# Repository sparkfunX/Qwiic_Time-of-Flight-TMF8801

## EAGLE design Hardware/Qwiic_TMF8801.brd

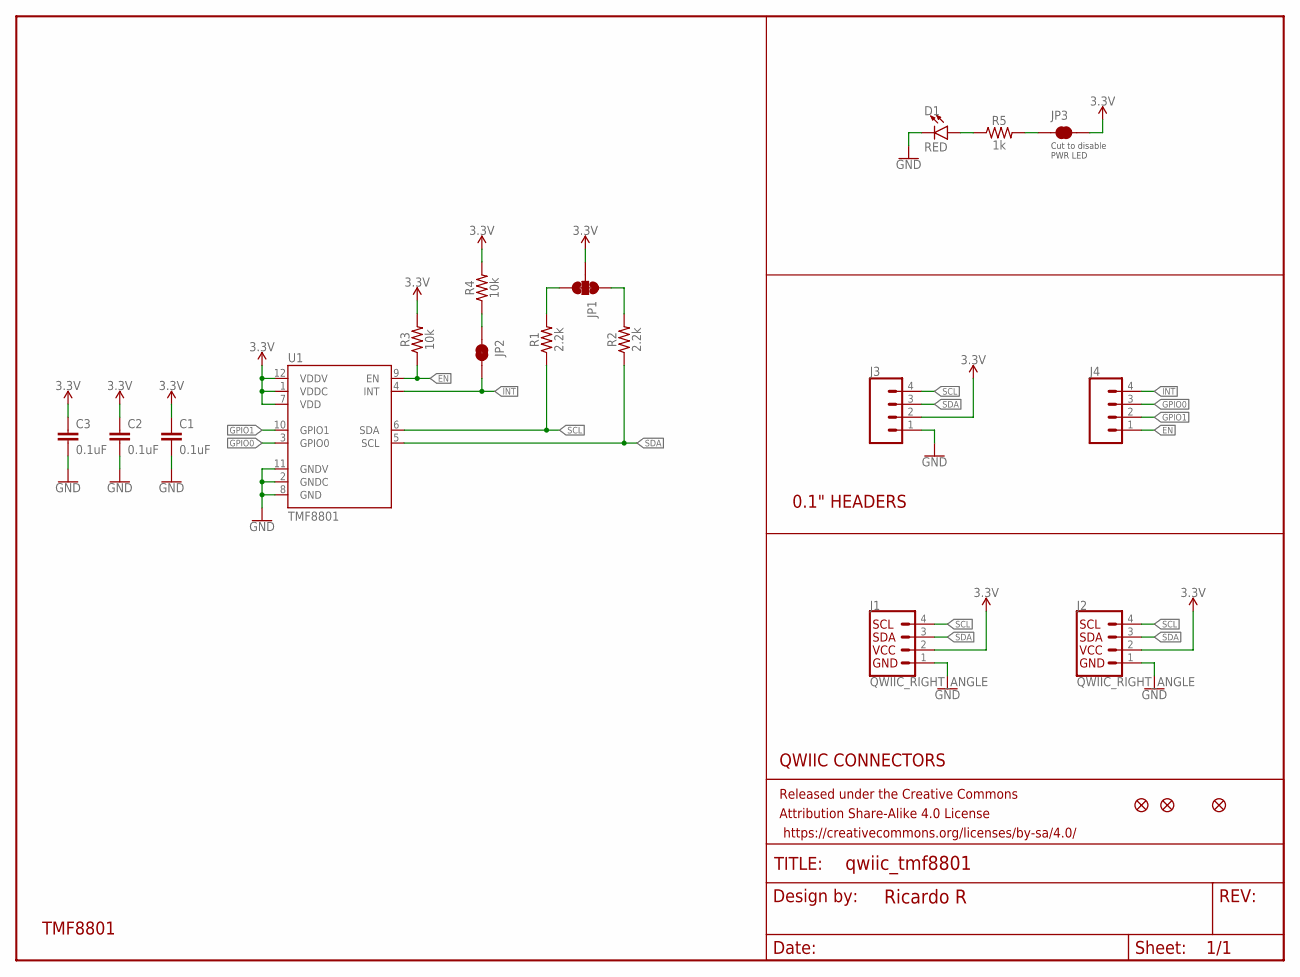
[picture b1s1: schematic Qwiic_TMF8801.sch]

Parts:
C1, C2, C3: 0.1uF; 0603
D1: RED; LED-0603
FD1, FD3, FD4: FIDUCIAL1X2; FIDUCIAL-1X2
FRAME1: FRAME-LETTERNO_PACKAGE; DUMMY
J1, J2: QWIIC_RIGHT_ANGLE; JST04_1MM_RA
J3, J4: CONN_041X04_NO_SILK; 1X04_NO_SILK
JP1: JUMPER-SMT_3_2-NC_TRACE_SILK; SMT-JUMPER_3_2-NC_TRACE_SILK
JP2, JP3: JUMPER-SMT_2_NC_TRACE_SILK; SMT-JUMPER_2_NC_TRACE_SILK
R1, R2: 2.2k; 0603
R3, R4: 10k; 0603
R5: 1k; 0603
U1: TMF8801; TMF8801-CUSTOM

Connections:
3.3V: C1.1, C2.1, C3.1, J1.2, J2.2, J3.2, JP1.2, JP3.2, R3.2, R4.2, U1.1 (VDDC), U1.7 (VDD), U1.12 (VDDV)
!INT: J4.4, JP2.2, U1.4 (INT)
EN: J4.1, R3.1, U1.9 (EN)
GND: C1.2, C2.2, C3.2, D1.C, J1.1, J2.1, J3.1, U1.2 (GNDC), U1.8 (GND), U1.11 (GNDV)
GPIO0: J4.3, U1.3 (GPIO0)
GPIO1: J4.2, U1.10 (GPIO1)
unnamed: D1.A, R5.1
unnamed: JP1.3, R1.2
unnamed: JP1.1, R2.2
unnamed: JP3.1, R5.2
unnamed: JP2.1, R4.1
SCL: J1.4, J2.4, J3.4, R1.1, U1.6 (SDA)
SDA: J1.3, J2.3, J3.3, R2.1, U1.5 (SCL)

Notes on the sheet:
QWIIC CONNECTORS
0.1" HEADERS
Cut to disable PWR LED
TMF8801

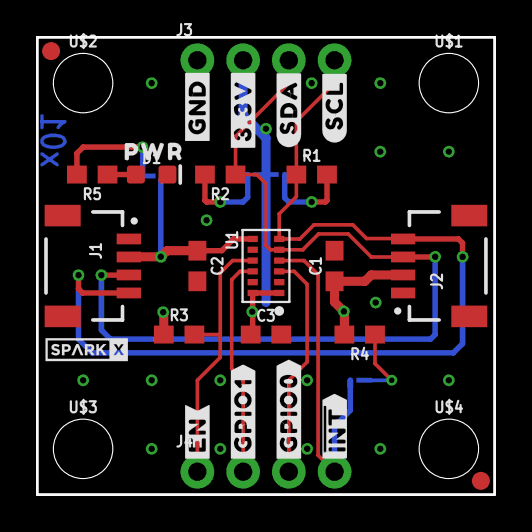
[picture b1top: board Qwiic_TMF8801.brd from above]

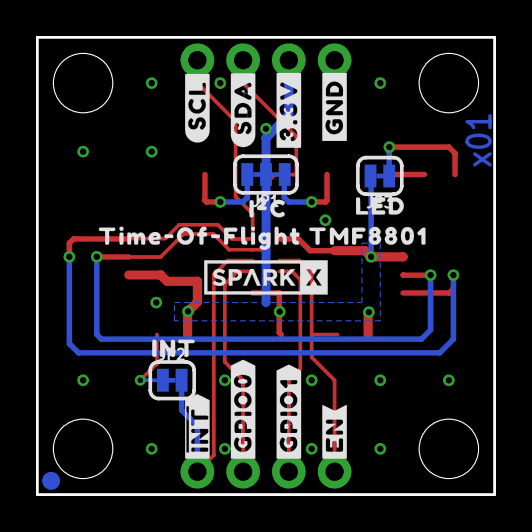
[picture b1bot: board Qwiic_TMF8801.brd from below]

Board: 2 copper layers, 25.4 x 25.4 mm, 48 parts (17 on the bottom side), 13 nets.

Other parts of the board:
U$1, U$2, U$3, U$4: STAND-OFF
U$5, U$17: #3#3V#1
U$6, U$19: #SDA#4
U$7, U$18: #GND#0
U$8, U$24: ##INT##7
U$9, U$25: #GPIO0#7
U$10, U$26: #GPIO1#7
U$11, U$23: #EN#6
U$12: #INT0
U$16: TIME#OF#FLIGHT_TMF88018
U$20: SPARKX-TINY
U$21, U$22: #SCL#5
U$27: SPARKX-SMALL
U$28: I�C0
U$29: LED1
U$30: PWR2

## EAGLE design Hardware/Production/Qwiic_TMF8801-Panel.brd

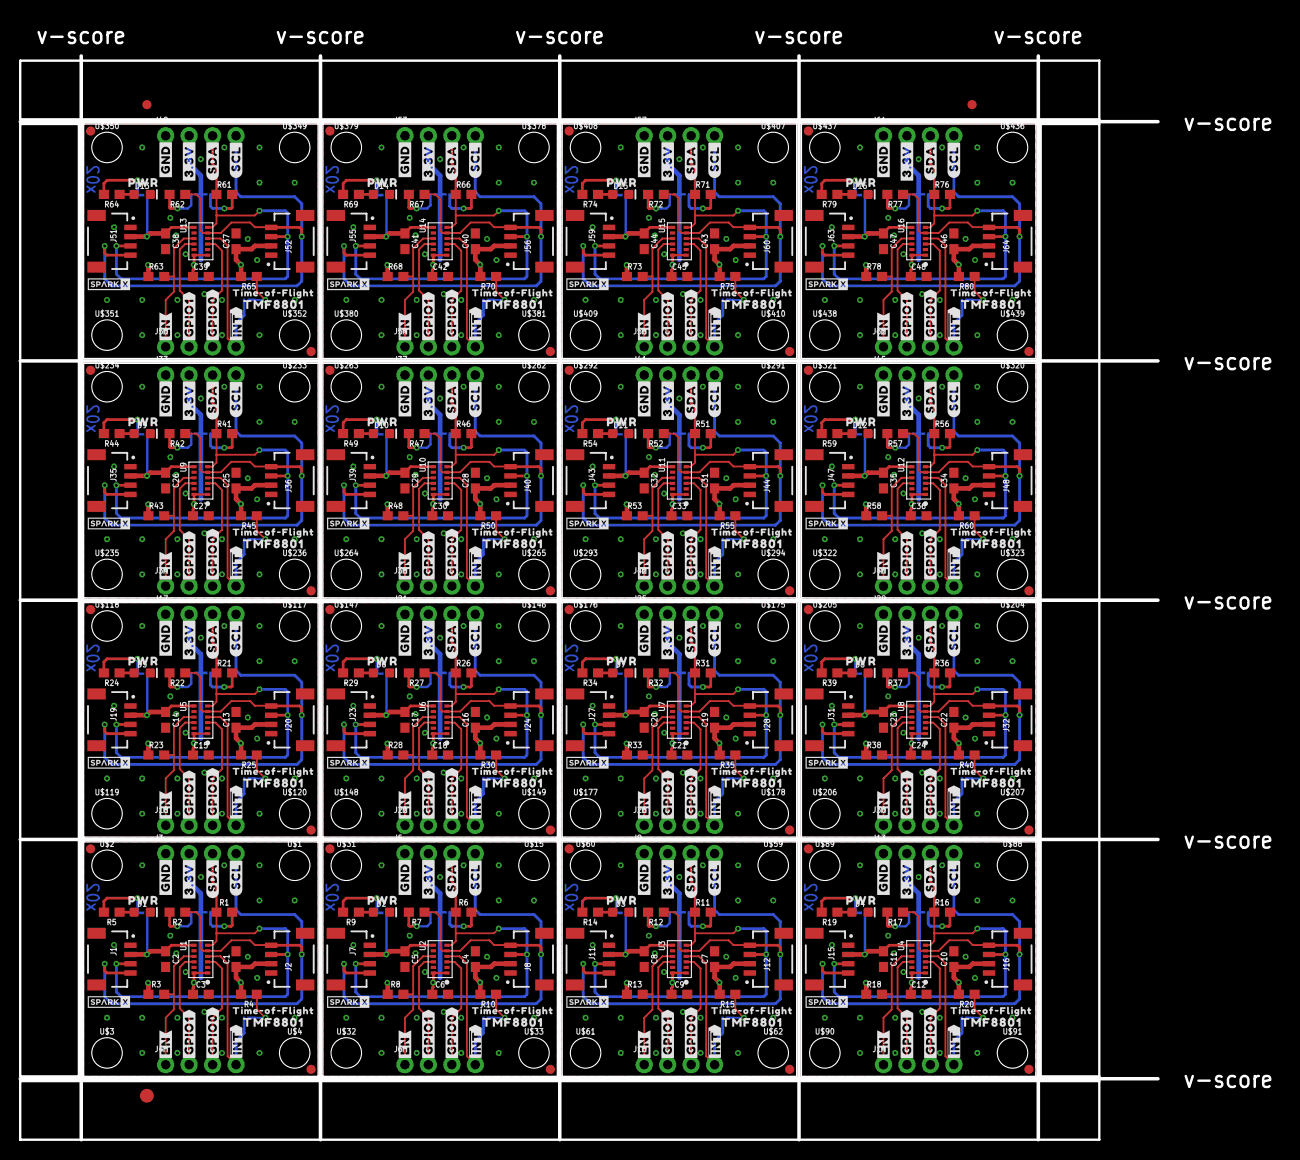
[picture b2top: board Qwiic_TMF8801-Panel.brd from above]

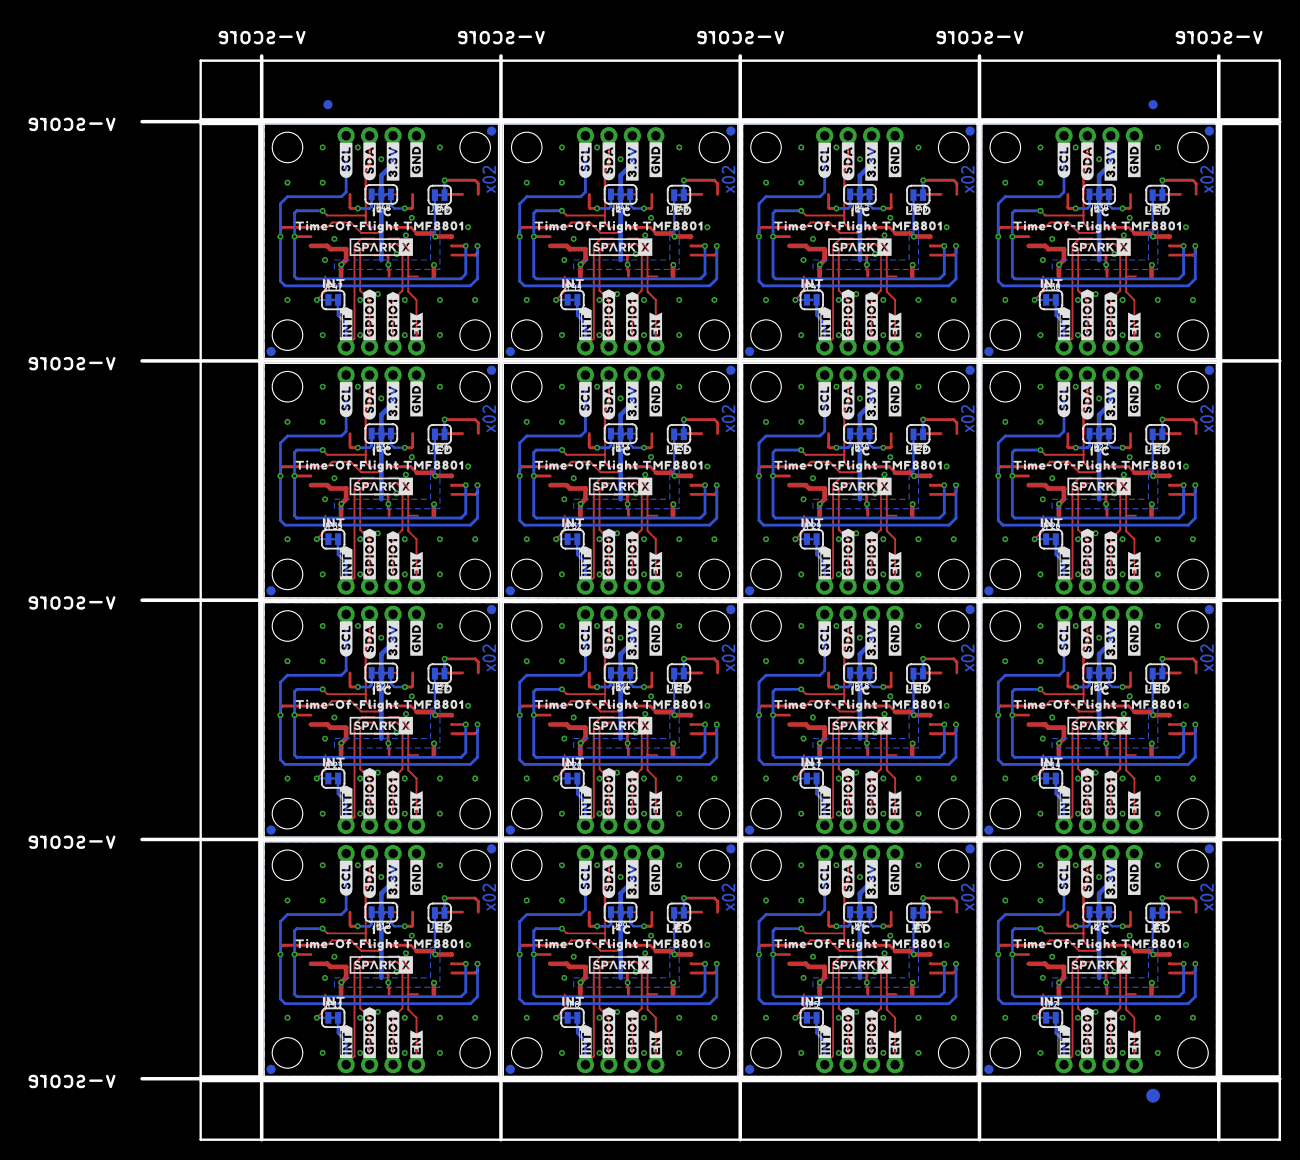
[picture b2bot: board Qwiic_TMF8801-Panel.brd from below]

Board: 2 copper layers, 123.2 x 117.3 mm, 822 parts (291 on the bottom side), 208 nets.

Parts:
C1, C2, C3, C4, C5, C6, C7, C8, C9, C10, C11, C12, C13, C14, C15, C16, C17, C18, C19, C20, C21, C22, C23, C24, C25, C26, C27, C28, C29, C30, C31, C32, C33, C34, C35, C36, C37, C38, C39, C40, C41, C42, C43, C44, C45, C46, C47, C48: 0.1uF; 0603
D1, D2, D3, D4, D5, D6, D7, D8, D9, D10, D11, D12, D13, D14, D15, D16: RED; LED-0603
E$1, E$2, E$3, E$4: FIDUCIAL-1X2
E$5, E$6: FIDUCIAL-1.5X3
FD1, FD2, FD3, FD4, FD5, FD6, FD7, FD8, FD9, FD10, FD11, FD12, FD13, FD14, FD15, FD16, FD17, FD18, FD19, FD20, FD21, FD22, FD23, FD24, FD25, FD26, FD27, FD28, FD29, FD30, FD31, FD32, FD33, FD34, FD35, FD36, FD37, FD38, FD39, FD40, FD41, FD42, FD43, FD44, FD45, FD46, FD47, FD48, FD49, FD50, FD51, FD52, FD53, FD54, FD55, FD56, FD57, FD58, FD59, FD60, FD61, FD62, FD63, FD64: FIDUCIAL1X2; FIDUCIAL-1X2
FRAME1, FRAME2, FRAME3, FRAME4, FRAME5, FRAME6, FRAME7, FRAME8, FRAME9, FRAME10, FRAME11, FRAME12, FRAME13, FRAME14, FRAME15, FRAME16: FRAME-LETTERNO_PACKAGE; DUMMY
J1, J2, J7, J8, J11, J12, J15, J16, J19, J20, J23, J24, J27, J28, J31, J32, J35, J36, J39, J40, J43, J44, J47, J48, J51, J52, J55, J56, J59, J60, J63, J64: Qwiic; JST04_1MM_RA
J3, J4, J5, J6, J9, J10, J13, J14, J17, J18, J21, J22, J25, J26, J29, J30, J33, J34, J37, J38, J41, J42, J45, J46, J49, J50, J53, J54, J57, J58, J61, J62: 1X04_NO_SILK
JP1, JP6, JP9, JP12, JP15, JP18, JP21, JP24, JP27, JP30, JP33, JP36, JP39, JP42, JP45, JP48: JUMPER-SMT_3_2-NC_TRACE_SILK; SMT-JUMPER_3_2-NC_TRACE_SILK
JP2, JP3, JP4, JP5, JP7, JP8, JP10, JP11, JP13, JP14, JP16, JP17, JP19, JP20, JP22, JP23, JP25, JP26, JP28, JP29, JP31, JP32, JP34, JP35, JP37, JP38, JP40, JP41, JP43, JP44, JP46, JP47: JUMPER-SMT_2_NC_TRACE_SILK; SMT-JUMPER_2_NC_TRACE_SILK
R1, R2, R6, R7, R11, R12, R16, R17, R21, R22, R26, R27, R31, R32, R36, R37, R41, R42, R46, R47, R51, R52, R56, R57, R61, R62, R66, R67, R71, R72, R76, R77: 2.2k; 0603
R3, R4, R8, R10, R13, R15, R18, R20, R23, R25, R28, R30, R33, R35, R38, R40, R43, R45, R48, R50, R53, R55, R58, R60, R63, R65, R68, R70, R73, R75, R78, R80: 10k; 0603
R5, R9, R14, R19, R24, R29, R34, R39, R44, R49, R54, R59, R64, R69, R74, R79: 1k; 0603
U1, U2, U3, U4, U5, U6, U7, U8, U9, U10, U11, U12, U13, U14, U15, U16: TMF8801; TMF8801-CUSTOM
U$1, U$2, U$3, U$4, U$15, U$31, U$32, U$33, U$59, U$60, U$61, U$62, U$88, U$89, U$90, U$91, U$117, U$118, U$119, U$120, U$146, U$147, U$148, U$149, U$175, U$176, U$177, U$178, U$204, U$205, U$206, U$207, U$233, U$234, U$235, U$236, U$262, U$263, U$264, U$265, U$291, U$292, U$293, U$294, U$320, U$321, U$322, U$323, U$349, U$350, U$351, U$352, U$378, U$379, U$380, U$381, U$407, U$408, U$409, U$410, U$436, U$437, U$438, U$439: STAND-OFF
U$5, U$17, U$36, U$44, U$65, U$73, U$94, U$102, U$123, U$131, U$152, U$160, U$181, U$189, U$210, U$218, U$239, U$247, U$268, U$276, U$297, U$305, U$326, U$334, U$355, U$363, U$384, U$392, U$413, U$421, U$442, U$450: #3#3V#1
U$6, U$19, U$38, U$46, U$67, U$75, U$96, U$104, U$125, U$133, U$154, U$162, U$183, U$191, U$212, U$220, U$241, U$249, U$270, U$278, U$299, U$307, U$328, U$336, U$357, U$365, U$386, U$394, U$415, U$423, U$444, U$452: #SDA#4
U$7, U$18, U$37, U$45, U$66, U$74, U$95, U$103, U$124, U$132, U$153, U$161, U$182, U$190, U$211, U$219, U$240, U$248, U$269, U$277, U$298, U$306, U$327, U$335, U$356, U$364, U$385, U$393, U$414, U$422, U$443, U$451: #GND#0
U$8, U$24, U$39, U$50, U$68, U$79, U$97, U$108, U$126, U$137, U$155, U$166, U$184, U$195, U$213, U$224, U$242, U$253, U$271, U$282, U$300, U$311, U$329, U$340, U$358, U$369, U$387, U$398, U$416, U$427, U$445, U$456: ##INT##7
U$9, U$25, U$40, U$51, U$69, U$80, U$98, U$109, U$127, U$138, U$156, U$167, U$185, U$196, U$214, U$225, U$243, U$254, U$272, U$283, U$301, U$312, U$330, U$341, U$359, U$370, U$388, U$399, U$417, U$428, U$446, U$457: #GPIO0#7
U$10, U$26, U$41, U$52, U$70, U$81, U$99, U$110, U$128, U$139, U$157, U$168, U$186, U$197, U$215, U$226, U$244, U$255, U$273, U$284, U$302, U$313, U$331, U$342, U$360, U$371, U$389, U$400, U$418, U$429, U$447, U$458: #GPIO1#7
U$11, U$23, U$42, U$49, U$71, U$78, U$100, U$107, U$129, U$136, U$158, U$165, U$187, U$194, U$216, U$223, U$245, U$252, U$274, U$281, U$303, U$310, U$332, U$339, U$361, U$368, U$390, U$397, U$419, U$426, U$448, U$455: #EN#6
U$12, U$56, U$85, U$114, U$143, U$172, U$201, U$230, U$259, U$288, U$317, U$346, U$375, U$404, U$433, U$462: #INT0
U$13, U$57, U$86, U$115, U$144, U$173, U$202, U$231, U$260, U$289, U$318, U$347, U$376, U$405, U$434, U$463: TMF88010
U$14, U$58, U$87, U$116, U$145, U$174, U$203, U$232, U$261, U$290, U$319, U$348, U$377, U$406, U$435, U$464: TIME#OF#FLIGHT0
U$16, U$43, U$72, U$101, U$130, U$159, U$188, U$217, U$246, U$275, U$304, U$333, U$362, U$391, U$420, U$449: TIME#OF#FLIGHT_TMF88018
U$20, U$34, U$63, U$92, U$121, U$150, U$179, U$208, U$237, U$266, U$295, U$324, U$353, U$382, U$411, U$440: SPARKX-TINY
U$21, U$22, U$47, U$48, U$76, U$77, U$105, U$106, U$134, U$135, U$163, U$164, U$192, U$193, U$221, U$222, U$250, U$251, U$279, U$280, U$308, U$309, U$337, U$338, U$366, U$367, U$395, U$396, U$424, U$425, U$453, U$454: #SCL#5
U$27, U$35, U$64, U$93, U$122, U$151, U$180, U$209, U$238, U$267, U$296, U$325, U$354, U$383, U$412, U$441: SPARKX-SMALL
U$28, U$53, U$82, U$111, U$140, U$169, U$198, U$227, U$256, U$285, U$314, U$343, U$372, U$401, U$430, U$459: I�C0
U$29, U$54, U$83, U$112, U$141, U$170, U$199, U$228, U$257, U$286, U$315, U$344, U$373, U$402, U$431, U$460: LED1
U$30, U$55, U$84, U$113, U$142, U$171, U$200, U$229, U$258, U$287, U$316, U$345, U$374, U$403, U$432, U$461: PWR2

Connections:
3.3V: C1.1, C2.1, C3.1, J1.2, J2.2, J3.2, JP1.2, JP3.2, R3.2, R4.2, U1.1, U1.7, U1.12
3.3V1: C4.1, C5.1, C6.1, J5.2, J7.2, J8.2, JP4.2, JP6.2, R8.2, R10.2, U2.1, U2.7, U2.12
3.3V2: C7.1, C8.1, C9.1, J9.2, J11.2, J12.2, JP7.2, JP9.2, R13.2, R15.2, U3.1, U3.7, U3.12
3.3V3: C10.1, C11.1, C12.1, J13.2, J15.2, J16.2, JP10.2, JP12.2, R18.2, R20.2, U4.1, U4.7, U4.12
3.3V4: C13.1, C14.1, C15.1, J17.2, J19.2, J20.2, JP13.2, JP15.2, R23.2, R25.2, U5.1, U5.7, U5.12
3.3V5: C16.1, C17.1, C18.1, J21.2, J23.2, J24.2, JP16.2, JP18.2, R28.2, R30.2, U6.1, U6.7, U6.12
3.3V6: C19.1, C20.1, C21.1, J25.2, J27.2, J28.2, JP19.2, JP21.2, R33.2, R35.2, U7.1, U7.7, U7.12
3.3V7: C22.1, C23.1, C24.1, J29.2, J31.2, J32.2, JP22.2, JP24.2, R38.2, R40.2, U8.1, U8.7, U8.12
3.3V8: C25.1, C26.1, C27.1, J33.2, J35.2, J36.2, JP25.2, JP27.2, R43.2, R45.2, U9.1, U9.7, U9.12
3.3V9: C28.1, C29.1, C30.1, J37.2, J39.2, J40.2, JP28.2, JP30.2, R48.2, R50.2, U10.1, U10.7, U10.12
3.3V10: C31.1, C32.1, C33.1, J41.2, J43.2, J44.2, JP31.2, JP33.2, R53.2, R55.2, U11.1, U11.7, U11.12
3.3V11: C34.1, C35.1, C36.1, J45.2, J47.2, J48.2, JP34.2, JP36.2, R58.2, R60.2, U12.1, U12.7, U12.12
3.3V12: C37.1, C38.1, C39.1, J49.2, J51.2, J52.2, JP37.2, JP39.2, R63.2, R65.2, U13.1, U13.7, U13.12
3.3V13: C40.1, C41.1, C42.1, J53.2, J55.2, J56.2, JP40.2, JP42.2, R68.2, R70.2, U14.1, U14.7, U14.12
3.3V14: C43.1, C44.1, C45.1, J57.2, J59.2, J60.2, JP43.2, JP45.2, R73.2, R75.2, U15.1, U15.7, U15.12
3.3V15: C46.1, C47.1, C48.1, J61.2, J63.2, J64.2, JP46.2, JP48.2, R78.2, R80.2, U16.1, U16.7, U16.12
!INT: J4.4, JP2.2, U1.4
!INT1: J6.4, JP5.2, U2.4
!INT2: J10.4, JP8.2, U3.4
!INT3: J14.4, JP11.2, U4.4
!INT4: J18.4, JP14.2, U5.4
!INT5: J22.4, JP17.2, U6.4
!INT6: J26.4, JP20.2, U7.4
!INT7: J30.4, JP23.2, U8.4
!INT8: J34.4, JP26.2, U9.4
!INT9: J38.4, JP29.2, U10.4
!INT10: J42.4, JP32.2, U11.4
!INT11: J46.4, JP35.2, U12.4
!INT12: J50.4, JP38.2, U13.4
!INT13: J54.4, JP41.2, U14.4
!INT14: J58.4, JP44.2, U15.4
!INT15: J62.4, JP47.2, U16.4
EN: J4.1, R3.1, U1.9
EN1: J6.1, R8.1, U2.9
EN2: J10.1, R13.1, U3.9
EN3: J14.1, R18.1, U4.9
EN4: J18.1, R23.1, U5.9
EN5: J22.1, R28.1, U6.9
EN6: J26.1, R33.1, U7.9
EN7: J30.1, R38.1, U8.9
EN8: J34.1, R43.1, U9.9
EN9: J38.1, R48.1, U10.9
EN10: J42.1, R53.1, U11.9
EN11: J46.1, R58.1, U12.9
EN12: J50.1, R63.1, U13.9
EN13: J54.1, R68.1, U14.9
EN14: J58.1, R73.1, U15.9
EN15: J62.1, R78.1, U16.9
GND: C1.2, C2.2, C3.2, D1.C, J1.1, J2.1, J3.1, U1.2, U1.8, U1.11
GND1: C4.2, C5.2, C6.2, D2.C, J5.1, J7.1, J8.1, U2.2, U2.8, U2.11
GND2: C7.2, C8.2, C9.2, D3.C, J9.1, J11.1, J12.1, U3.2, U3.8, U3.11
GND3: C10.2, C11.2, C12.2, D4.C, J13.1, J15.1, J16.1, U4.2, U4.8, U4.11
GND4: C13.2, C14.2, C15.2, D5.C, J17.1, J19.1, J20.1, U5.2, U5.8, U5.11
GND5: C16.2, C17.2, C18.2, D6.C, J21.1, J23.1, J24.1, U6.2, U6.8, U6.11
GND6: C19.2, C20.2, C21.2, D7.C, J25.1, J27.1, J28.1, U7.2, U7.8, U7.11
GND7: C22.2, C23.2, C24.2, D8.C, J29.1, J31.1, J32.1, U8.2, U8.8, U8.11
GND8: C25.2, C26.2, C27.2, D9.C, J33.1, J35.1, J36.1, U9.2, U9.8, U9.11
GND9: C28.2, C29.2, C30.2, D10.C, J37.1, J39.1, J40.1, U10.2, U10.8, U10.11
GND10: C31.2, C32.2, C33.2, D11.C, J41.1, J43.1, J44.1, U11.2, U11.8, U11.11
GND11: C34.2, C35.2, C36.2, D12.C, J45.1, J47.1, J48.1, U12.2, U12.8, U12.11
GND12: C37.2, C38.2, C39.2, D13.C, J49.1, J51.1, J52.1, U13.2, U13.8, U13.11
GND13: C40.2, C41.2, C42.2, D14.C, J53.1, J55.1, J56.1, U14.2, U14.8, U14.11
GND14: C43.2, C44.2, C45.2, D15.C, J57.1, J59.1, J60.1, U15.2, U15.8, U15.11
GND15: C46.2, C47.2, C48.2, D16.C, J61.1, J63.1, J64.1, U16.2, U16.8, U16.11
GPIO0: J4.3, U1.3
GPIO1: J4.2, U1.10
GPIO2: J6.2, U2.10
GPIO3: J6.3, U2.3
GPIO4: J10.2, U3.10
GPIO5: J10.3, U3.3
GPIO6: J14.2, U4.10
GPIO7: J14.3, U4.3
GPIO8: J18.2, U5.10
GPIO9: J18.3, U5.3
GPIO10: J22.2, U6.10
GPIO11: J22.3, U6.3
GPIO12: J26.2, U7.10
GPIO13: J26.3, U7.3
GPIO14: J30.2, U8.10
GPIO15: J30.3, U8.3
GPIO16: J34.2, U9.10
GPIO17: J34.3, U9.3
GPIO18: J38.2, U10.10
GPIO19: J38.3, U10.3
GPIO20: J42.2, U11.10
GPIO21: J42.3, U11.3
GPIO22: J46.2, U12.10
GPIO23: J46.3, U12.3
GPIO24: J50.2, U13.10
GPIO25: J50.3, U13.3
GPIO26: J54.2, U14.10
GPIO27: J54.3, U14.3
GPIO28: J58.2, U15.10
GPIO29: J58.3, U15.3
GPIO30: J62.2, U16.10
GPIO31: J62.3, U16.3
unnamed: D1.A, R5.1
unnamed: JP1.3, R1.2
unnamed: JP1.1, R2.2
unnamed: JP3.1, R5.2
unnamed: JP2.1, R4.1
unnamed: JP6.3, R6.2
unnamed: JP6.1, R7.2
unnamed: D2.A, R9.1
unnamed: JP4.1, R9.2
unnamed: JP5.1, R10.1
unnamed: JP9.3, R11.2
unnamed: JP9.1, R12.2
unnamed: D3.A, R14.1
unnamed: JP7.1, R14.2
unnamed: JP8.1, R15.1
unnamed: JP12.3, R16.2
unnamed: JP12.1, R17.2
unnamed: D4.A, R19.1
unnamed: JP10.1, R19.2
unnamed: JP11.1, R20.1
unnamed: JP15.3, R21.2
unnamed: JP15.1, R22.2
unnamed: D5.A, R24.1
unnamed: JP13.1, R24.2
unnamed: JP14.1, R25.1
unnamed: JP18.3, R26.2
unnamed: JP18.1, R27.2
unnamed: D6.A, R29.1
unnamed: JP16.1, R29.2
unnamed: JP17.1, R30.1
unnamed: JP21.3, R31.2
unnamed: JP21.1, R32.2
unnamed: D7.A, R34.1
unnamed: JP19.1, R34.2
unnamed: JP20.1, R35.1
unnamed: JP24.3, R36.2
unnamed: JP24.1, R37.2
unnamed: D8.A, R39.1
unnamed: JP22.1, R39.2
unnamed: JP23.1, R40.1
unnamed: JP27.3, R41.2
unnamed: JP27.1, R42.2
unnamed: D9.A, R44.1
unnamed: JP25.1, R44.2
unnamed: JP26.1, R45.1
unnamed: JP30.3, R46.2
unnamed: JP30.1, R47.2
unnamed: D10.A, R49.1
unnamed: JP28.1, R49.2
unnamed: JP29.1, R50.1
unnamed: JP33.3, R51.2
unnamed: JP33.1, R52.2
unnamed: D11.A, R54.1
unnamed: JP31.1, R54.2
unnamed: JP32.1, R55.1
unnamed: JP36.3, R56.2
unnamed: JP36.1, R57.2
unnamed: D12.A, R59.1
unnamed: JP34.1, R59.2
unnamed: JP35.1, R60.1
unnamed: JP39.3, R61.2
unnamed: JP39.1, R62.2
unnamed: D13.A, R64.1
unnamed: JP37.1, R64.2
unnamed: JP38.1, R65.1
unnamed: JP42.3, R66.2
unnamed: JP42.1, R67.2
unnamed: D14.A, R69.1
unnamed: JP40.1, R69.2
unnamed: JP41.1, R70.1
unnamed: JP45.3, R71.2
unnamed: JP45.1, R72.2
unnamed: D15.A, R74.1
unnamed: JP43.1, R74.2
unnamed: JP44.1, R75.1
unnamed: JP48.3, R76.2
unnamed: JP48.1, R77.2
unnamed: D16.A, R79.1
unnamed: JP46.1, R79.2
unnamed: JP47.1, R80.1
SCL: J1.4, J2.4, J3.4, R2.1, U1.5
SCL1: J5.4, J7.4, J8.4, R7.1, U2.5
SCL2: J9.4, J11.4, J12.4, R12.1, U3.5
SCL3: J13.4, J15.4, J16.4, R17.1, U4.5
SCL4: J17.4, J19.4, J20.4, R22.1, U5.5
SCL5: J21.4, J23.4, J24.4, R27.1, U6.5
SCL6: J25.4, J27.4, J28.4, R32.1, U7.5
SCL7: J29.4, J31.4, J32.4, R37.1, U8.5
SCL8: J33.4, J35.4, J36.4, R42.1, U9.5
SCL9: J37.4, J39.4, J40.4, R47.1, U10.5
SCL10: J41.4, J43.4, J44.4, R52.1, U11.5
SCL11: J45.4, J47.4, J48.4, R57.1, U12.5
SCL12: J49.4, J51.4, J52.4, R62.1, U13.5
SCL13: J53.4, J55.4, J56.4, R67.1, U14.5
SCL14: J57.4, J59.4, J60.4, R72.1, U15.5
SCL15: J61.4, J63.4, J64.4, R77.1, U16.5
SDA: J1.3, J2.3, J3.3, R1.1, U1.6
SDA1: J5.3, J7.3, J8.3, R6.1, U2.6
SDA2: J9.3, J11.3, J12.3, R11.1, U3.6
SDA3: J13.3, J15.3, J16.3, R16.1, U4.6
SDA4: J17.3, J19.3, J20.3, R21.1, U5.6
SDA5: J21.3, J23.3, J24.3, R26.1, U6.6
SDA6: J25.3, J27.3, J28.3, R31.1, U7.6
SDA7: J29.3, J31.3, J32.3, R36.1, U8.6
SDA8: J33.3, J35.3, J36.3, R41.1, U9.6
SDA9: J37.3, J39.3, J40.3, R46.1, U10.6
SDA10: J41.3, J43.3, J44.3, R51.1, U11.6
SDA11: J45.3, J47.3, J48.3, R56.1, U12.6
SDA12: J49.3, J51.3, J52.3, R61.1, U13.6
SDA13: J53.3, J55.3, J56.3, R66.1, U14.6
SDA14: J57.3, J59.3, J60.3, R71.1, U15.6
SDA15: J61.3, J63.3, J64.3, R76.1, U16.6

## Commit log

2020-11-13 First version
2020-11-20 Add files via upload
    Updated SCH file per Nathan's feedback
2020-11-20 Add files via upload
    Added missing documents folder
2020-11-24 Add files via upload
    Added missing libraries and labels; changed design per Nathan's feedback and SparfFun design guidelines
2020-11-24 Moved components back onto grid.
2020-11-25 Layout changes
    Changed board layout per Nathan's feedback.
2020-11-26 Added missing frame to schematic; removed extra fiducial
2020-12-02 Fixed airwires, added silk to top. Added production panel.
2020-12-02 Remove extra files. Add ignore.
2020-12-02 Remove old files
2020-12-03 Added gitignore file
2020-12-30 Removed backup files
2021-01-20 Fixed inverted SCL and SDA files; created panelized version.
2021-02-16 Added updated datasheets and preliminary library version
2021-02-17 Added GPIO pins functionality; added programmable sampling rate funcionality
2021-02-19 Updated library and sketch
2021-02-22 Added comments to code; added 2 examples out of 5
2021-02-24 Removed sampling period functions; fixed GPIO set/reset functions.
2021-02-24 Updated comments
2021-02-25 Created calibration data example. Fixed calibration data routine timeout.
2021-02-27 Added missing Arduino.h file in library; created interrupt sketch example.
2021-03-01 Renamed example files to be consistent with SparkFun's existing ones. Added extra comments on select ino files.
2021-03-24 Fixed library naming
2021-04-16 Removing software. Duplicated in library.
2021-04-17 Added README.md
2021-04-17 Added LICENSE.md

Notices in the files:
parts and their libraries:
SparkFun-Jumpers: Licensing: Creative Commons ShareAlike 4.0 International - https://creativecommons.org/licenses/by-sa/4.0
SparkFun-Aesthetics: Released under the Creative Commons Attribution Share-Alike 4.0 License
SparkFun-Aesthetics: https://creativecommons.org/licenses/by-sa/4.0
